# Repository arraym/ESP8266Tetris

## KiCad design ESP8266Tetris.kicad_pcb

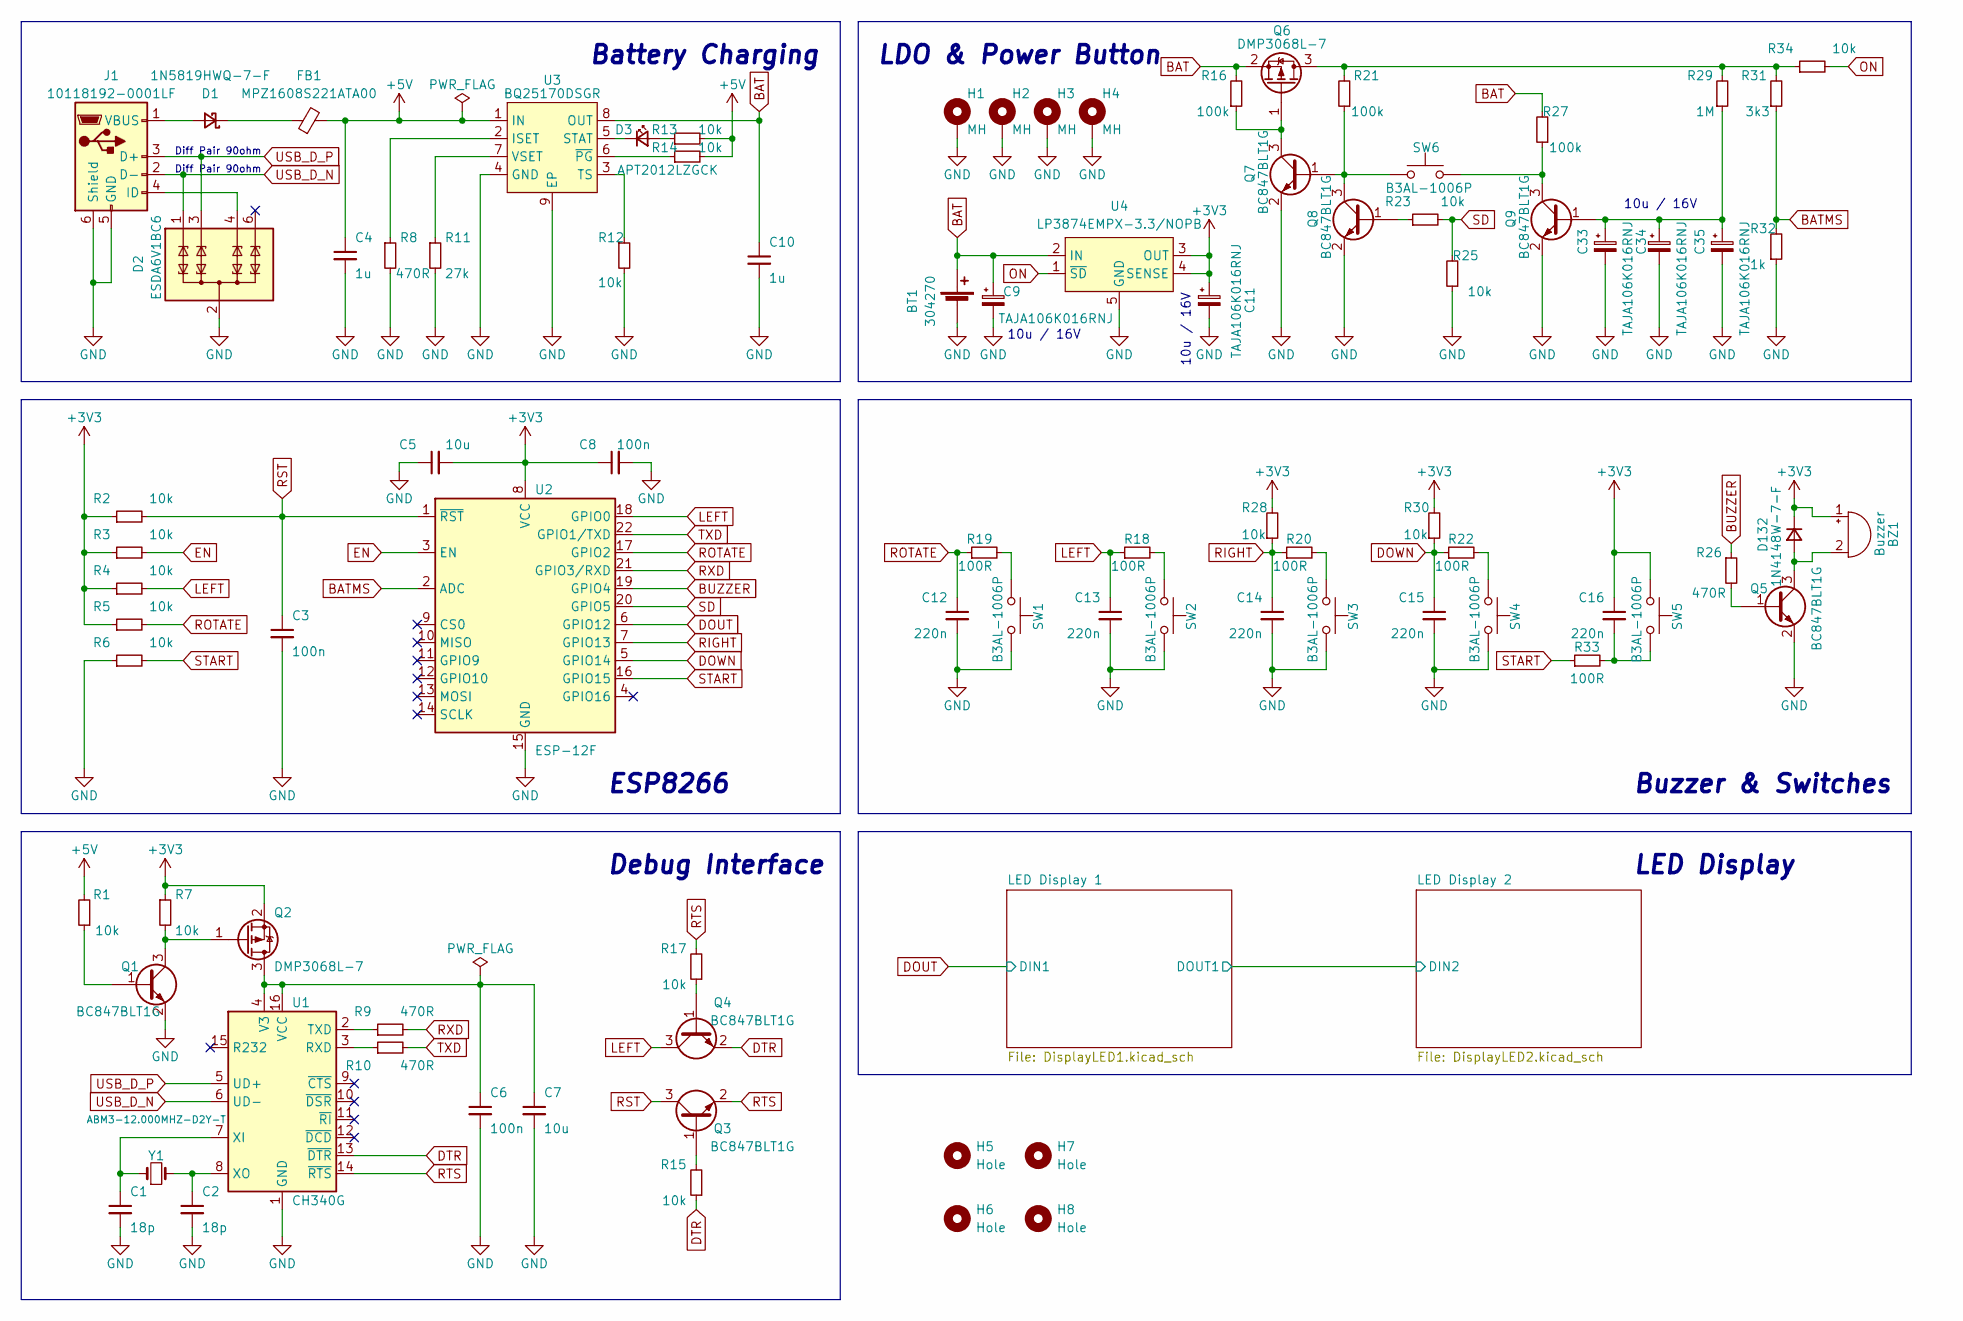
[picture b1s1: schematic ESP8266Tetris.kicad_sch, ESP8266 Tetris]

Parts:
BT1: 304270; Battery_LiPo_304270
BZ1: Buzzer; BUZZER_SMD
C1, C2: 18p; C_0603_1608Metric_Pad1.08x0.95mm_HandSolder
C3, C6, C8: 100n; C_0603_1608Metric_Pad1.08x0.95mm_HandSolder
C4, C10: 1u; C_0603_1608Metric_Pad1.08x0.95mm_HandSolder
C5, C7: 10u; C_0603_1608Metric_Pad1.08x0.95mm_HandSolder
C9, C11, C33, C34, C35: TAJA106K016RNJ; CP_EIA-3216-18_Kemet-A_Pad1.58x1.35mm_HandSolder
C12, C13, C14, C15, C16: 220n; C_0603_1608Metric_Pad1.08x0.95mm_HandSolder
D1: 1N5819HWQ-7-F; D_SOD-123
D2: ESDA6V1BC6; SOT-23-6
D3: APT2012LZGCK; LED_0805_2012Metric_Pad1.15x1.40mm_HandSolder
D132: 1N4148W-7-F; D_SOD-123
FB1: MPZ1608S221ATA00; L_0603_1608Metric_Pad1.05x0.95mm_HandSolder
H1, H2, H3, H4: MH; MountingHole_3.2mm_M3_DIN965_Pad
H5, H6, H7, H8: Hole; MountingHole_2.2mm_M2
J1: 10118192-0001LF; USB_Micro-B_Amphenol_10118192-0001LF_Horizontal
Q1, Q3, Q4, Q5, Q7, Q8, Q9: BC847BLT1G; SOT-23
Q2, Q6: DMP3068L-7; SOT-23
R1, R2, R3, R4, R5, R6, R7, R12, R13, R14, R15, R17, R23, R25, R28, R30, R34: 10k; R_0603_1608Metric_Pad0.98x0.95mm_HandSolder
R8, R9, R10, R26: 470R; R_0603_1608Metric_Pad0.98x0.95mm_HandSolder
R11: 27k; R_0603_1608Metric_Pad0.98x0.95mm_HandSolder
R16, R21, R27: 100k; R_0603_1608Metric_Pad0.98x0.95mm_HandSolder
R18, R19, R20, R22, R33: 100R; R_0603_1608Metric_Pad0.98x0.95mm_HandSolder
R29: 1M; R_0603_1608Metric_Pad0.98x0.95mm_HandSolder
R31: 3k3; R_0603_1608Metric_Pad0.98x0.95mm_HandSolder
R32: 1k; R_0603_1608Metric_Pad0.98x0.95mm_HandSolder
SW1, SW2, SW3, SW4, SW5, SW6: B3AL-1006P; SW_SPST_Omron_B3AL-100xP
U1: CH340G; SOIC-16_3.9x9.9mm_P1.27mm
U2: ESP-12F; ESP-12E
U3: BQ25170DSGR; WSON-8-1EP_2x2mm_P0.5mm_EP0.9x1.6mm_ThermalVias
U4: LP3874EMPX-3.3/NOPB; SOT-223-5
Y1: ABM3-12.000MHZ-D2Y-T; Crystal_SMD_7050-2Pin_7.0x5.0mm

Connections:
+3V3: BZ1.1 (-), C5.2, C8.1, C11.1, C16.1, D132.1 (K), Q2.2 (S), R2.1, R3.1, R4.1, R5.1, R7.1, R28.2, R30.2, SW5.1, U2.8 (VCC), U4.3 (OUT), U4.4 (SENSE); also elsewhere on the board
+5V: C4.1, FB1.2, R1.2, R13.2, R14.2, U3.1 (IN)
BAT: BT1.1 (+), C9.1, C10.1, Q6.2 (S), R16.2, R27.2, U3.8 (OUT), U4.2 (IN)
BATMS: R31.1, R32.2, U2.2 (ADC)
BUZZER: R26.1, U2.19 (GPIO4)
DOUT: U2.6 (GPIO12); also elsewhere on the board
DOWN: C15.1, R22.1, R30.1, U2.5 (GPIO14)
DTR: Q4.2 (E), R15.1, U1.13 (~DTR)
EN: R3.2, U2.3 (EN)
GND: BT1.2 (-), C1.2, C2.2, C3.2, C4.2, C5.1, C6.2, C7.2, C8.2, C9.2, C10.2, C11.2, C12.2, C13.2, C14.2, C15.2, C33.2, C34.2, C35.2, D2.2 (COM), D2.5 (COM), H1.1, H2.1, H3.1, H4.1, J1.5 (GND), J1.6 (Shield), Q1.2 (E), Q5.2 (E), Q7.2 (E), Q8.2 (E), Q9.2 (E), R6.1, R8.2, R11.2, R12.2, R25.1, R32.1, SW1.2, SW2.2, SW3.2, SW4.2, U1.1 (GND), U2.15 (GND), U3.4 (GND), U3.9 (EP), U4.5 (GND); also elsewhere on the board
LEFT: C13.1, Q4.3 (C), R4.2, R18.1, U2.18 (GPIO0)
unnamed: BZ1.2 (+), D132.2 (A), Q5.3 (C)
unnamed: C1.1, U1.7 (XI), Y1.1
unnamed: C2.1, U1.8 (XO), Y1.2
unnamed: C6.1, C7.1, Q2.3 (D), U1.4 (V3), U1.16 (VCC)
unnamed: C16.2, R33.2, SW5.2
unnamed: C33.1, C34.1, C35.1, Q9.1 (B), R29.1
unnamed: D1.1 (K), FB1.1
unnamed: D1.2 (A), J1.1 (VBUS)
unnamed: D2.4 (TVS3), J1.4 (ID)
unnamed: D3.1 (K), U3.5 (STAT)
unnamed: D3.2 (A), R13.1
unnamed: Q1.1 (B), R1.1
unnamed: Q1.3 (C), Q2.1 (G), R7.2
unnamed: Q3.1 (B), R15.2
unnamed: Q4.1 (B), R17.1
unnamed: Q5.1 (B), R26.2
unnamed: Q6.1 (G), Q7.3 (C), R16.1
unnamed: Q6.3 (D), R21.2, R29.2, R31.2, R34.1
unnamed: Q7.1 (B), Q8.3 (C), R21.1, SW6.1
unnamed: Q8.1 (B), R23.1
unnamed: Q9.3 (C), R27.1, SW6.2
unnamed: R8.1, U3.2 (ISET)
unnamed: R9.1, U1.2 (TXD)
unnamed: R10.1, U1.3 (RXD)
unnamed: R11.1, U3.7 (VSET)
unnamed: R12.1, U3.3 (TS)
unnamed: R14.1, U3.6 (~PG)
unnamed: R18.2, SW2.1
unnamed: R19.2, SW1.1
unnamed: R20.2, SW3.1
unnamed: R22.2, SW4.1
ON: R34.2, U4.1 (~SD)
RIGHT: C14.1, R20.1, R28.1, U2.7 (GPIO13)
ROTATE: C12.1, R5.2, R19.1, U2.17 (GPIO2)
RST: C3.1, Q3.3 (C), R2.2, U2.1 (~RST)
RTS: Q3.2 (E), R17.2, U1.14 (~RTS)
RXD: R9.2, U2.21 (GPIO3/RXD)
SD: R23.2, R25.2, U2.20 (GPIO5)
START: R6.2, R33.1, U2.16 (GPIO15)
TXD: R10.2, U2.22 (GPIO1/TXD)
USB_D_N: D2.1 (TVS1), J1.2 (D-), U1.6 (UD-)
USB_D_P: D2.3 (TVS2), J1.3 (D+), U1.5 (UD+)

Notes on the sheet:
ESP8266
Diff Pair 90ohm
10u / 16V
LDO & Power Button
Buzzer & Switches
Debug Interface
LED Display
Battery Charging

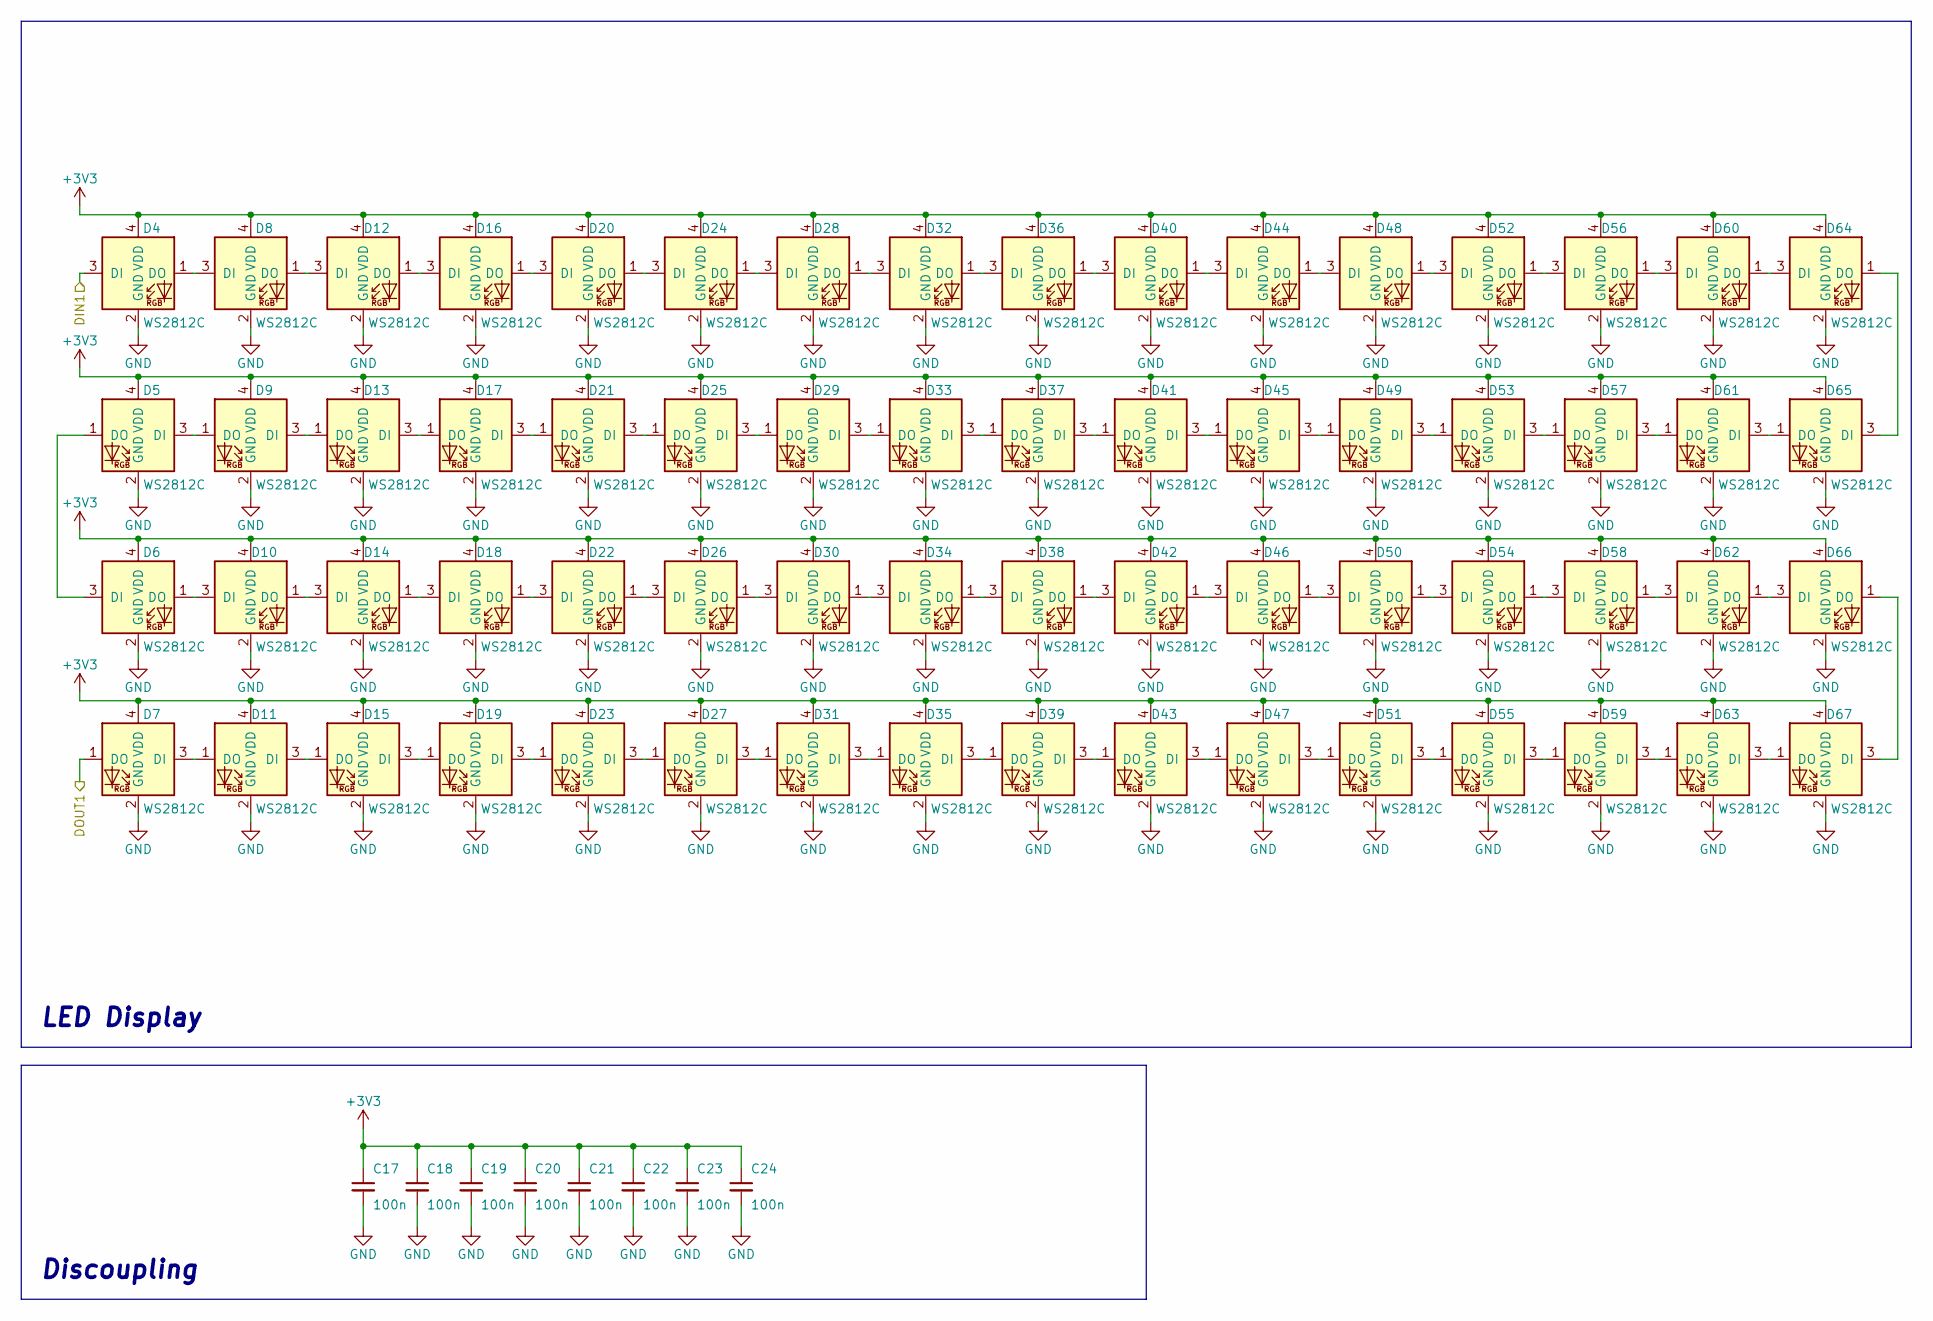
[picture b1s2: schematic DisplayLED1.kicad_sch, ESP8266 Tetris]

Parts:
C17, C18, C19, C20, C21, C22, C23, C24: 100n; C_0603_1608Metric_Pad1.08x0.95mm_HandSolder
D4, D5, D6, D7, D8, D9, D10, D11, D12, D13, D14, D15, D16, D17, D18, D19, D20, D21, D22, D23, D24, D25, D26, D27, D28, D29, D30, D31, D32, D33, D34, D35, D36, D37, D38, D39, D40, D41, D42, D43, D44, D45, D46, D47, D48, D49, D50, D51, D52, D53, D54, D55, D56, D57, D58, D59, D60, D61, D62, D63, D64, D65, D66, D67: WS2812C; WS2812-2020

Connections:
+3V3: C17.1, C18.1, C19.1, C20.1, C21.1, C22.1, C23.1, C24.1, D4.4 (VDD), D5.4 (VDD), D6.4 (VDD), D7.4 (VDD), D8.4 (VDD), D9.4 (VDD), D10.4 (VDD), D11.4 (VDD), D12.4 (VDD), D13.4 (VDD), D14.4 (VDD), D15.4 (VDD), D16.4 (VDD), D17.4 (VDD), D18.4 (VDD), D19.4 (VDD), D20.4 (VDD), D21.4 (VDD), D22.4 (VDD), D23.4 (VDD), D24.4 (VDD), D25.4 (VDD), D26.4 (VDD), D27.4 (VDD), D28.4 (VDD), D29.4 (VDD), D30.4 (VDD), D31.4 (VDD), D32.4 (VDD), D33.4 (VDD), D34.4 (VDD), D35.4 (VDD), D36.4 (VDD), D37.4 (VDD), D38.4 (VDD), D39.4 (VDD), D40.4 (VDD), D41.4 (VDD), D42.4 (VDD), D43.4 (VDD), D44.4 (VDD), D45.4 (VDD), D46.4 (VDD), D47.4 (VDD), D48.4 (VDD), D49.4 (VDD), D50.4 (VDD), D51.4 (VDD), D52.4 (VDD), D53.4 (VDD), D54.4 (VDD), D55.4 (VDD), D56.4 (VDD), D57.4 (VDD), D58.4 (VDD), D59.4 (VDD), D60.4 (VDD), D61.4 (VDD), D62.4 (VDD), D63.4 (VDD), D64.4 (VDD), D65.4 (VDD), D66.4 (VDD), D67.4 (VDD); also elsewhere on the board
/LED Display 1/DOUT1: D7.1 (DO); also elsewhere on the board
DOUT: D4.3 (DI); also elsewhere on the board
GND: C17.2, C18.2, C19.2, C20.2, C21.2, C22.2, C23.2, C24.2, D4.2 (GND), D5.2 (GND), D6.2 (GND), D7.2 (GND), D8.2 (GND), D9.2 (GND), D10.2 (GND), D11.2 (GND), D12.2 (GND), D13.2 (GND), D14.2 (GND), D15.2 (GND), D16.2 (GND), D17.2 (GND), D18.2 (GND), D19.2 (GND), D20.2 (GND), D21.2 (GND), D22.2 (GND), D23.2 (GND), D24.2 (GND), D25.2 (GND), D26.2 (GND), D27.2 (GND), D28.2 (GND), D29.2 (GND), D30.2 (GND), D31.2 (GND), D32.2 (GND), D33.2 (GND), D34.2 (GND), D35.2 (GND), D36.2 (GND), D37.2 (GND), D38.2 (GND), D39.2 (GND), D40.2 (GND), D41.2 (GND), D42.2 (GND), D43.2 (GND), D44.2 (GND), D45.2 (GND), D46.2 (GND), D47.2 (GND), D48.2 (GND), D49.2 (GND), D50.2 (GND), D51.2 (GND), D52.2 (GND), D53.2 (GND), D54.2 (GND), D55.2 (GND), D56.2 (GND), D57.2 (GND), D58.2 (GND), D59.2 (GND), D60.2 (GND), D61.2 (GND), D62.2 (GND), D63.2 (GND), D64.2 (GND), D65.2 (GND), D66.2 (GND), D67.2 (GND); also elsewhere on the board
unnamed: D4.1 (DO), D8.3 (DI)
unnamed: D5.1 (DO), D6.3 (DI)
unnamed: D5.3 (DI), D9.1 (DO)
unnamed: D10.1 (DO), D14.3 (DI)
unnamed: D6.1 (DO), D10.3 (DI)
unnamed: D7.3 (DI), D11.1 (DO)
unnamed: D11.3 (DI), D15.1 (DO)
unnamed: D12.1 (DO), D16.3 (DI)
unnamed: D8.1 (DO), D12.3 (DI)
unnamed: D9.3 (DI), D13.1 (DO)
unnamed: D13.3 (DI), D17.1 (DO)
unnamed: D14.1 (DO), D18.3 (DI)
unnamed: D15.3 (DI), D19.1 (DO)
unnamed: D16.1 (DO), D20.3 (DI)
unnamed: D17.3 (DI), D21.1 (DO)
unnamed: D18.1 (DO), D22.3 (DI)
unnamed: D19.3 (DI), D23.1 (DO)
unnamed: D20.1 (DO), D24.3 (DI)
unnamed: D21.3 (DI), D25.1 (DO)
unnamed: D22.1 (DO), D26.3 (DI)
unnamed: D23.3 (DI), D27.1 (DO)
unnamed: D24.1 (DO), D28.3 (DI)
unnamed: D25.3 (DI), D29.1 (DO)
unnamed: D26.1 (DO), D30.3 (DI)
unnamed: D27.3 (DI), D31.1 (DO)
unnamed: D28.1 (DO), D32.3 (DI)
unnamed: D29.3 (DI), D33.1 (DO)
unnamed: D30.1 (DO), D34.3 (DI)
unnamed: D31.3 (DI), D35.1 (DO)
unnamed: D32.1 (DO), D36.3 (DI)
unnamed: D33.3 (DI), D37.1 (DO)
unnamed: D34.1 (DO), D38.3 (DI)
unnamed: D35.3 (DI), D39.1 (DO)
unnamed: D36.1 (DO), D40.3 (DI)
unnamed: D37.3 (DI), D41.1 (DO)
unnamed: D38.1 (DO), D42.3 (DI)
unnamed: D39.3 (DI), D43.1 (DO)
unnamed: D40.1 (DO), D44.3 (DI)
unnamed: D41.3 (DI), D45.1 (DO)
unnamed: D42.1 (DO), D46.3 (DI)
unnamed: D43.3 (DI), D47.1 (DO)
unnamed: D44.1 (DO), D48.3 (DI)
unnamed: D45.3 (DI), D49.1 (DO)
unnamed: D46.1 (DO), D50.3 (DI)
unnamed: D47.3 (DI), D51.1 (DO)
unnamed: D48.1 (DO), D52.3 (DI)
unnamed: D49.3 (DI), D53.1 (DO)
unnamed: D50.1 (DO), D54.3 (DI)
unnamed: D51.3 (DI), D55.1 (DO)
unnamed: D52.1 (DO), D56.3 (DI)
unnamed: D53.3 (DI), D57.1 (DO)
unnamed: D54.1 (DO), D58.3 (DI)
unnamed: D55.3 (DI), D59.1 (DO)
unnamed: D56.1 (DO), D60.3 (DI)
unnamed: D57.3 (DI), D61.1 (DO)
unnamed: D58.1 (DO), D62.3 (DI)
unnamed: D59.3 (DI), D63.1 (DO)
unnamed: D60.1 (DO), D64.3 (DI)
unnamed: D61.3 (DI), D65.1 (DO)
unnamed: D62.1 (DO), D66.3 (DI)
unnamed: D63.3 (DI), D67.1 (DO)
unnamed: D64.1 (DO), D65.3 (DI)
unnamed: D66.1 (DO), D67.3 (DI)

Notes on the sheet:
Discoupling
LED Display

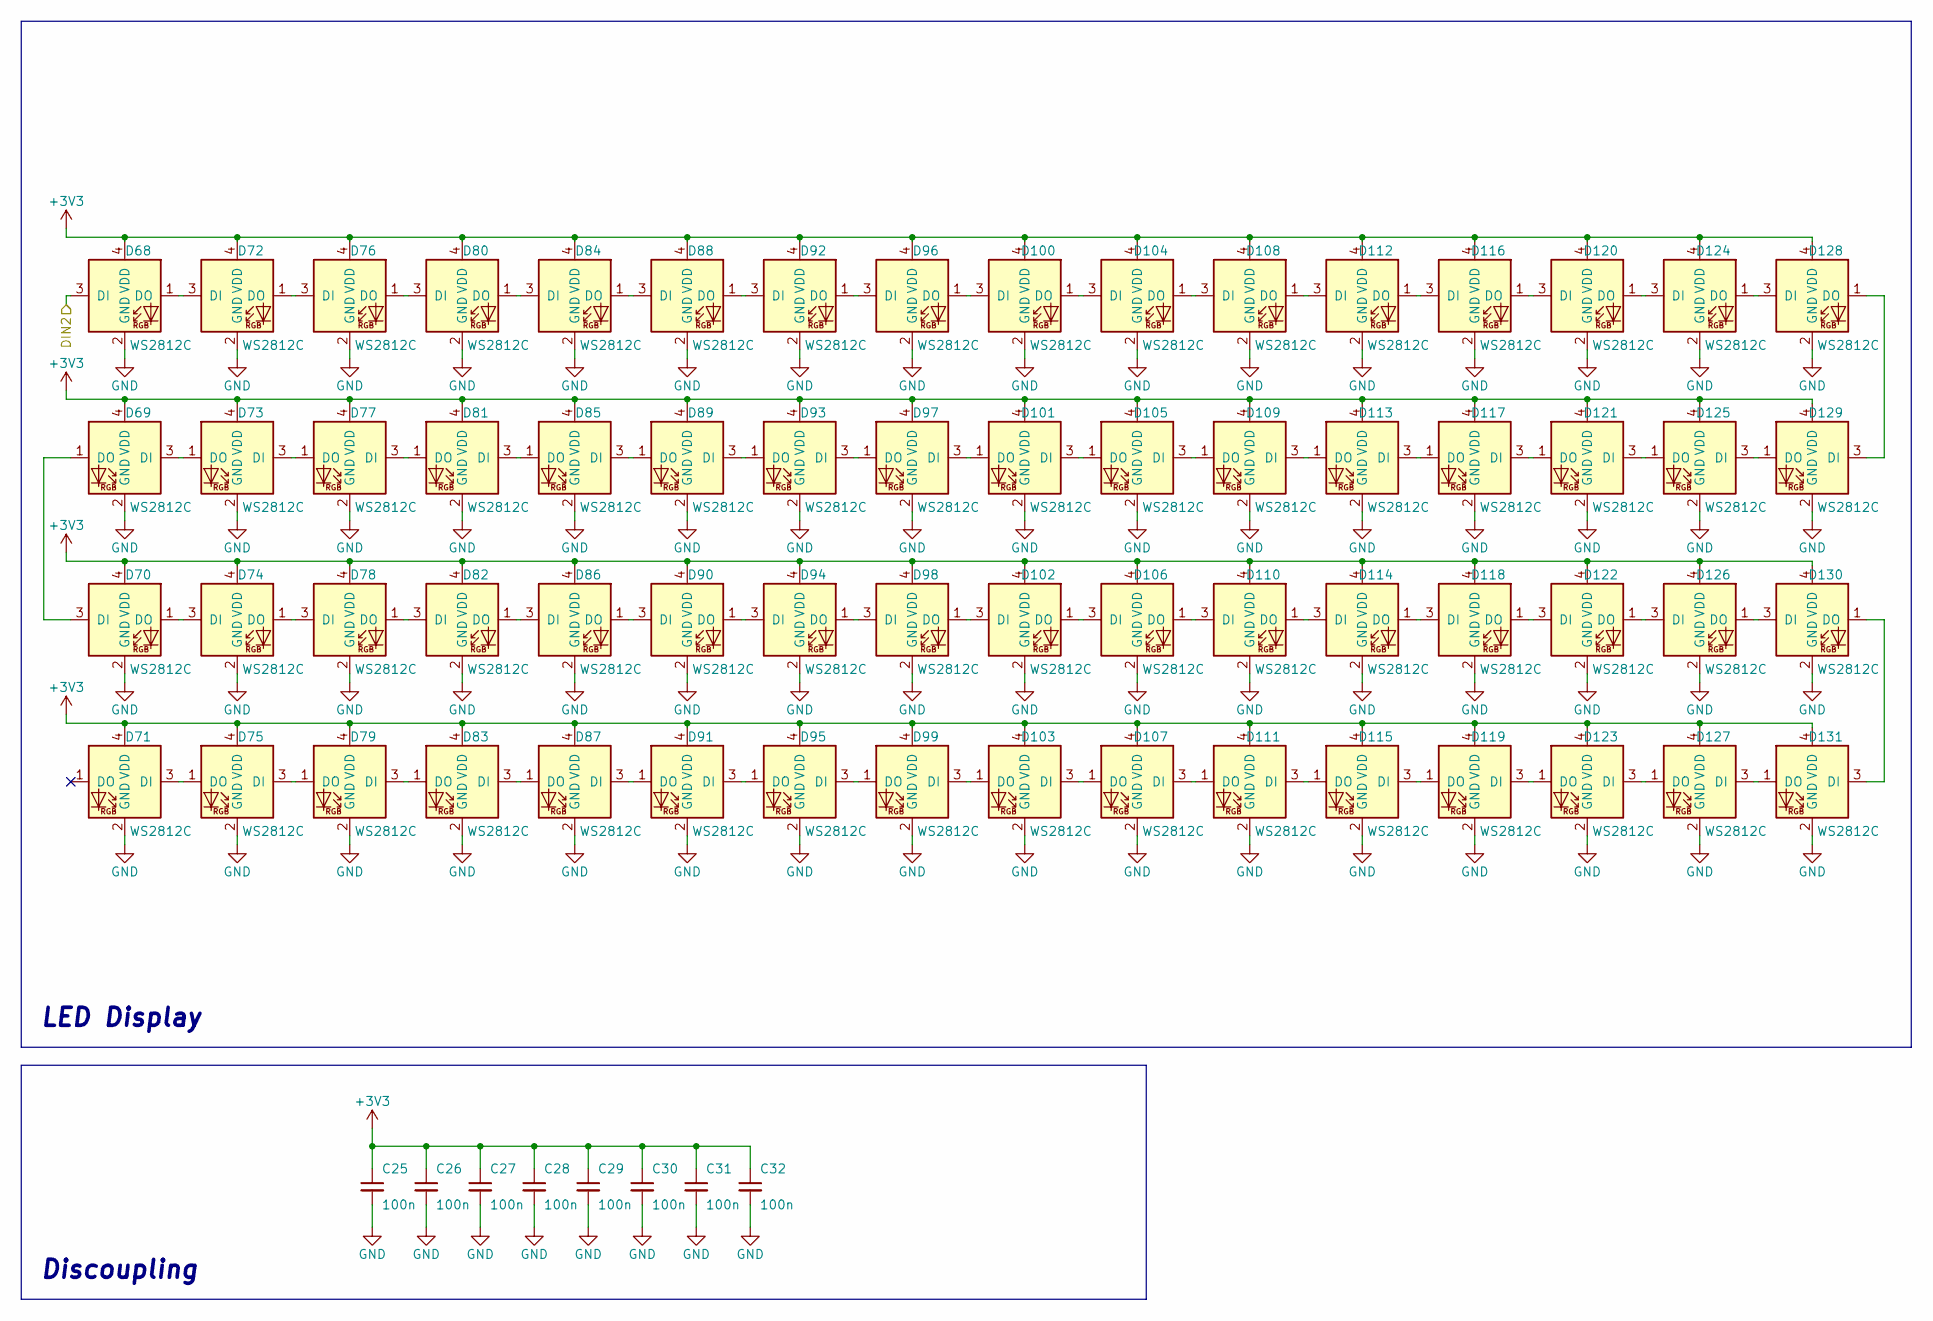
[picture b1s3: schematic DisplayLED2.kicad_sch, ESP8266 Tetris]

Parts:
C25, C26, C27, C28, C29, C30, C31, C32: 100n; C_0603_1608Metric_Pad1.08x0.95mm_HandSolder
D68, D69, D70, D71, D72, D73, D74, D75, D76, D77, D78, D79, D80, D81, D82, D83, D84, D85, D86, D87, D88, D89, D90, D91, D92, D93, D94, D95, D96, D97, D98, D99, D100, D101, D102, D103, D104, D105, D106, D107, D108, D109, D110, D111, D112, D113, D114, D115, D116, D117, D118, D119, D120, D121, D122, D123, D124, D125, D126, D127, D128, D129, D130, D131: WS2812C; WS2812-2020

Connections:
+3V3: C25.1, C26.1, C27.1, C28.1, C29.1, C30.1, C31.1, C32.1, D68.4 (VDD), D69.4 (VDD), D70.4 (VDD), D71.4 (VDD), D72.4 (VDD), D73.4 (VDD), D74.4 (VDD), D75.4 (VDD), D76.4 (VDD), D77.4 (VDD), D78.4 (VDD), D79.4 (VDD), D80.4 (VDD), D81.4 (VDD), D82.4 (VDD), D83.4 (VDD), D84.4 (VDD), D85.4 (VDD), D86.4 (VDD), D87.4 (VDD), D88.4 (VDD), D89.4 (VDD), D90.4 (VDD), D91.4 (VDD), D92.4 (VDD), D93.4 (VDD), D94.4 (VDD), D95.4 (VDD), D96.4 (VDD), D97.4 (VDD), D98.4 (VDD), D99.4 (VDD), D100.4 (VDD), D101.4 (VDD), D102.4 (VDD), D103.4 (VDD), D104.4 (VDD), D105.4 (VDD), D106.4 (VDD), D107.4 (VDD), D108.4 (VDD), D109.4 (VDD), D110.4 (VDD), D111.4 (VDD), D112.4 (VDD), D113.4 (VDD), D114.4 (VDD), D115.4 (VDD), D116.4 (VDD), D117.4 (VDD), D118.4 (VDD), D119.4 (VDD), D120.4 (VDD), D121.4 (VDD), D122.4 (VDD), D123.4 (VDD), D124.4 (VDD), D125.4 (VDD), D126.4 (VDD), D127.4 (VDD), D128.4 (VDD), D129.4 (VDD), D130.4 (VDD), D131.4 (VDD); also elsewhere on the board
/LED Display 1/DOUT1: D68.3 (DI); also elsewhere on the board
GND: C25.2, C26.2, C27.2, C28.2, C29.2, C30.2, C31.2, C32.2, D68.2 (GND), D69.2 (GND), D70.2 (GND), D71.2 (GND), D72.2 (GND), D73.2 (GND), D74.2 (GND), D75.2 (GND), D76.2 (GND), D77.2 (GND), D78.2 (GND), D79.2 (GND), D80.2 (GND), D81.2 (GND), D82.2 (GND), D83.2 (GND), D84.2 (GND), D85.2 (GND), D86.2 (GND), D87.2 (GND), D88.2 (GND), D89.2 (GND), D90.2 (GND), D91.2 (GND), D92.2 (GND), D93.2 (GND), D94.2 (GND), D95.2 (GND), D96.2 (GND), D97.2 (GND), D98.2 (GND), D99.2 (GND), D100.2 (GND), D101.2 (GND), D102.2 (GND), D103.2 (GND), D104.2 (GND), D105.2 (GND), D106.2 (GND), D107.2 (GND), D108.2 (GND), D109.2 (GND), D110.2 (GND), D111.2 (GND), D112.2 (GND), D113.2 (GND), D114.2 (GND), D115.2 (GND), D116.2 (GND), D117.2 (GND), D118.2 (GND), D119.2 (GND), D120.2 (GND), D121.2 (GND), D122.2 (GND), D123.2 (GND), D124.2 (GND), D125.2 (GND), D126.2 (GND), D127.2 (GND), D128.2 (GND), D129.2 (GND), D130.2 (GND), D131.2 (GND); also elsewhere on the board
unnamed: D68.1 (DO), D72.3 (DI)
unnamed: D69.1 (DO), D70.3 (DI)
unnamed: D69.3 (DI), D73.1 (DO)
unnamed: D70.1 (DO), D74.3 (DI)
unnamed: D71.3 (DI), D75.1 (DO)
unnamed: D72.1 (DO), D76.3 (DI)
unnamed: D73.3 (DI), D77.1 (DO)
unnamed: D74.1 (DO), D78.3 (DI)
unnamed: D75.3 (DI), D79.1 (DO)
unnamed: D76.1 (DO), D80.3 (DI)
unnamed: D77.3 (DI), D81.1 (DO)
unnamed: D78.1 (DO), D82.3 (DI)
unnamed: D79.3 (DI), D83.1 (DO)
unnamed: D80.1 (DO), D84.3 (DI)
unnamed: D81.3 (DI), D85.1 (DO)
unnamed: D82.1 (DO), D86.3 (DI)
unnamed: D83.3 (DI), D87.1 (DO)
unnamed: D84.1 (DO), D88.3 (DI)
unnamed: D85.3 (DI), D89.1 (DO)
unnamed: D86.1 (DO), D90.3 (DI)
unnamed: D87.3 (DI), D91.1 (DO)
unnamed: D88.1 (DO), D92.3 (DI)
unnamed: D89.3 (DI), D93.1 (DO)
unnamed: D90.1 (DO), D94.3 (DI)
unnamed: D91.3 (DI), D95.1 (DO)
unnamed: D92.1 (DO), D96.3 (DI)
unnamed: D93.3 (DI), D97.1 (DO)
unnamed: D94.1 (DO), D98.3 (DI)
unnamed: D95.3 (DI), D99.1 (DO)
unnamed: D100.1 (DO), D104.3 (DI)
unnamed: D96.1 (DO), D100.3 (DI)
unnamed: D97.3 (DI), D101.1 (DO)
unnamed: D101.3 (DI), D105.1 (DO)
unnamed: D102.1 (DO), D106.3 (DI)
unnamed: D98.1 (DO), D102.3 (DI)
unnamed: D99.3 (DI), D103.1 (DO)
unnamed: D103.3 (DI), D107.1 (DO)
unnamed: D104.1 (DO), D108.3 (DI)
unnamed: D105.3 (DI), D109.1 (DO)
unnamed: D106.1 (DO), D110.3 (DI)
unnamed: D107.3 (DI), D111.1 (DO)
unnamed: D108.1 (DO), D112.3 (DI)
unnamed: D109.3 (DI), D113.1 (DO)
unnamed: D110.1 (DO), D114.3 (DI)
unnamed: D111.3 (DI), D115.1 (DO)
unnamed: D112.1 (DO), D116.3 (DI)
unnamed: D113.3 (DI), D117.1 (DO)
unnamed: D114.1 (DO), D118.3 (DI)
unnamed: D115.3 (DI), D119.1 (DO)
unnamed: D116.1 (DO), D120.3 (DI)
unnamed: D117.3 (DI), D121.1 (DO)
unnamed: D118.1 (DO), D122.3 (DI)
unnamed: D119.3 (DI), D123.1 (DO)
unnamed: D120.1 (DO), D124.3 (DI)
unnamed: D121.3 (DI), D125.1 (DO)
unnamed: D122.1 (DO), D126.3 (DI)
unnamed: D123.3 (DI), D127.1 (DO)
unnamed: D124.1 (DO), D128.3 (DI)
unnamed: D125.3 (DI), D129.1 (DO)
unnamed: D126.1 (DO), D130.3 (DI)
unnamed: D127.3 (DI), D131.1 (DO)
unnamed: D128.1 (DO), D129.3 (DI)
unnamed: D130.1 (DO), D131.3 (DI)

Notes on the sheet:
LED Display
Discoupling

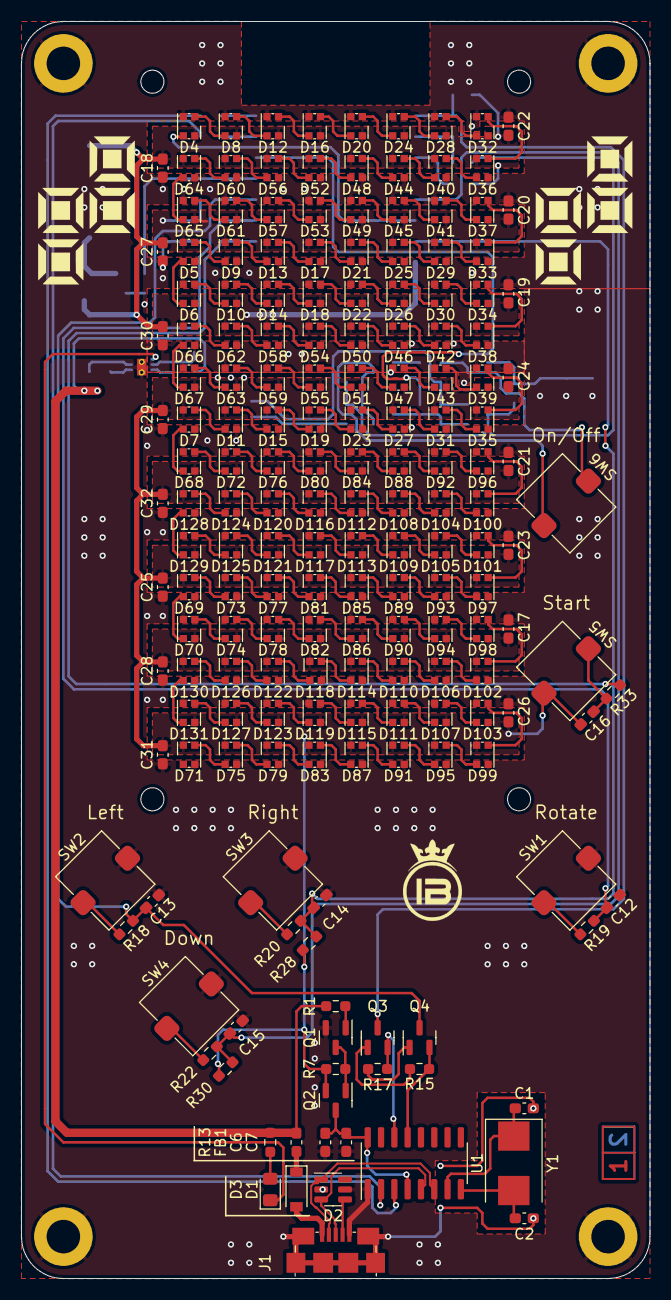
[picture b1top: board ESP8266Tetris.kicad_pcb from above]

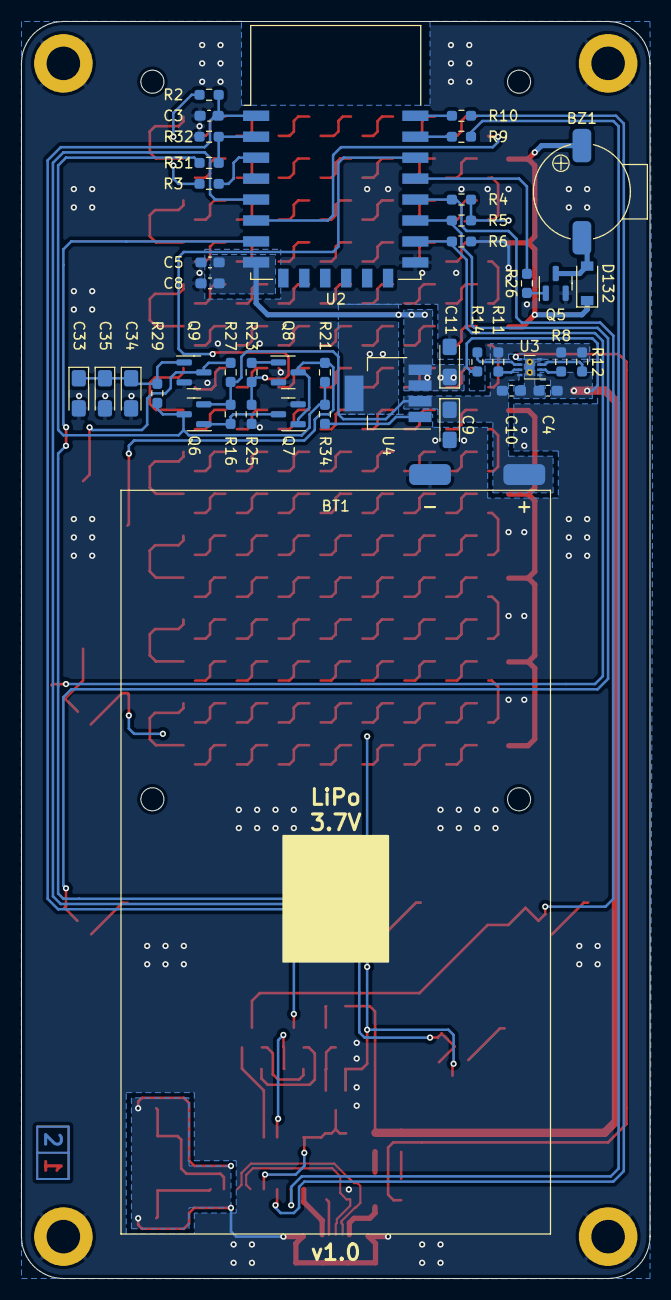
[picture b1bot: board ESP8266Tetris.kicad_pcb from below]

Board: 2 copper layers, 60.0 x 120.0 mm, 232 parts (42 on the bottom side), 180 nets.

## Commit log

2022-09-11 Initial commit.
2022-09-13 Battery charge and 3.3V LDO circuits changed, new datasheets added.
2022-09-18 LEDs added to schematic, footprints assigned, PCB layout started.
2022-09-20 Soft letching power switch circuit added, buttons reassigned to GPIOs.
2022-09-24 Schematic finished, routing PCB started.
2022-10-02 Routing PCB done.
2022-10-04 Fabrication and assembly files generated (v1.0).
2022-10-06 Buzzer moved to bottom layer, fabrication and assembly files regenerated.
2022-11-25 Two lines removed from top silk screen, F_Silkscreen gerber file regenerated.
2023-01-20 Buttons debounce capacitors value changed from 10n to 220n.
2023-02-15 Interactive BOM updated.
2023-02-16 Device pictures added.
